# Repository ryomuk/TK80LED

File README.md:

# TK80LED
TK-80互換機(ZK-80P)用LED表示盤(TK-80 flavor LED board for ZK-80P)

## 概要
オレンジピコショップで売られているTK-80互換機(ZK-80 ポケット(ZK-80P))用の表示盤
「TK-80 flavor LED board for ZK-80P」です．

オリジナルのキットの表示がTK-80っぽくなかったので，SN713を使って本物っぽくしてみました．
ZK-80ポケット(ZK-80P)用です．ZK-80には対応していません．

私が勝手に作ったもので，ZK-80, ZK-80Pの作者様やピコソフト様とは無関係です．

## 基板
配線パターン，LED配置，シルクはかなり実機に似せたこだわりの作り(笑)になっています．

## ファームウェア書き換えについて
ZK-80PはMAX7219の輝度の設定値が小さいので，そのままの設定でSN713を駆動するとかなり暗いです．
明るくするためには，ZK-80Pのファームウェアを書き換えが必要です．
ファームウェアの書き換えについては下記のブログをご参照下さい．

ファームウェア書き換え後

実機との比較

ファームウェア書き換え前

## 関連ブログ
 - [ZK-80(TK-80互換機)のLED改装](https://blog.goo.ne.jp/tk-80/e/5548a42761d789a6131d8d7753d236a3)

## 免責事項
- 本機によってZK-80Pに不具合等が発生しても一切関知しません．

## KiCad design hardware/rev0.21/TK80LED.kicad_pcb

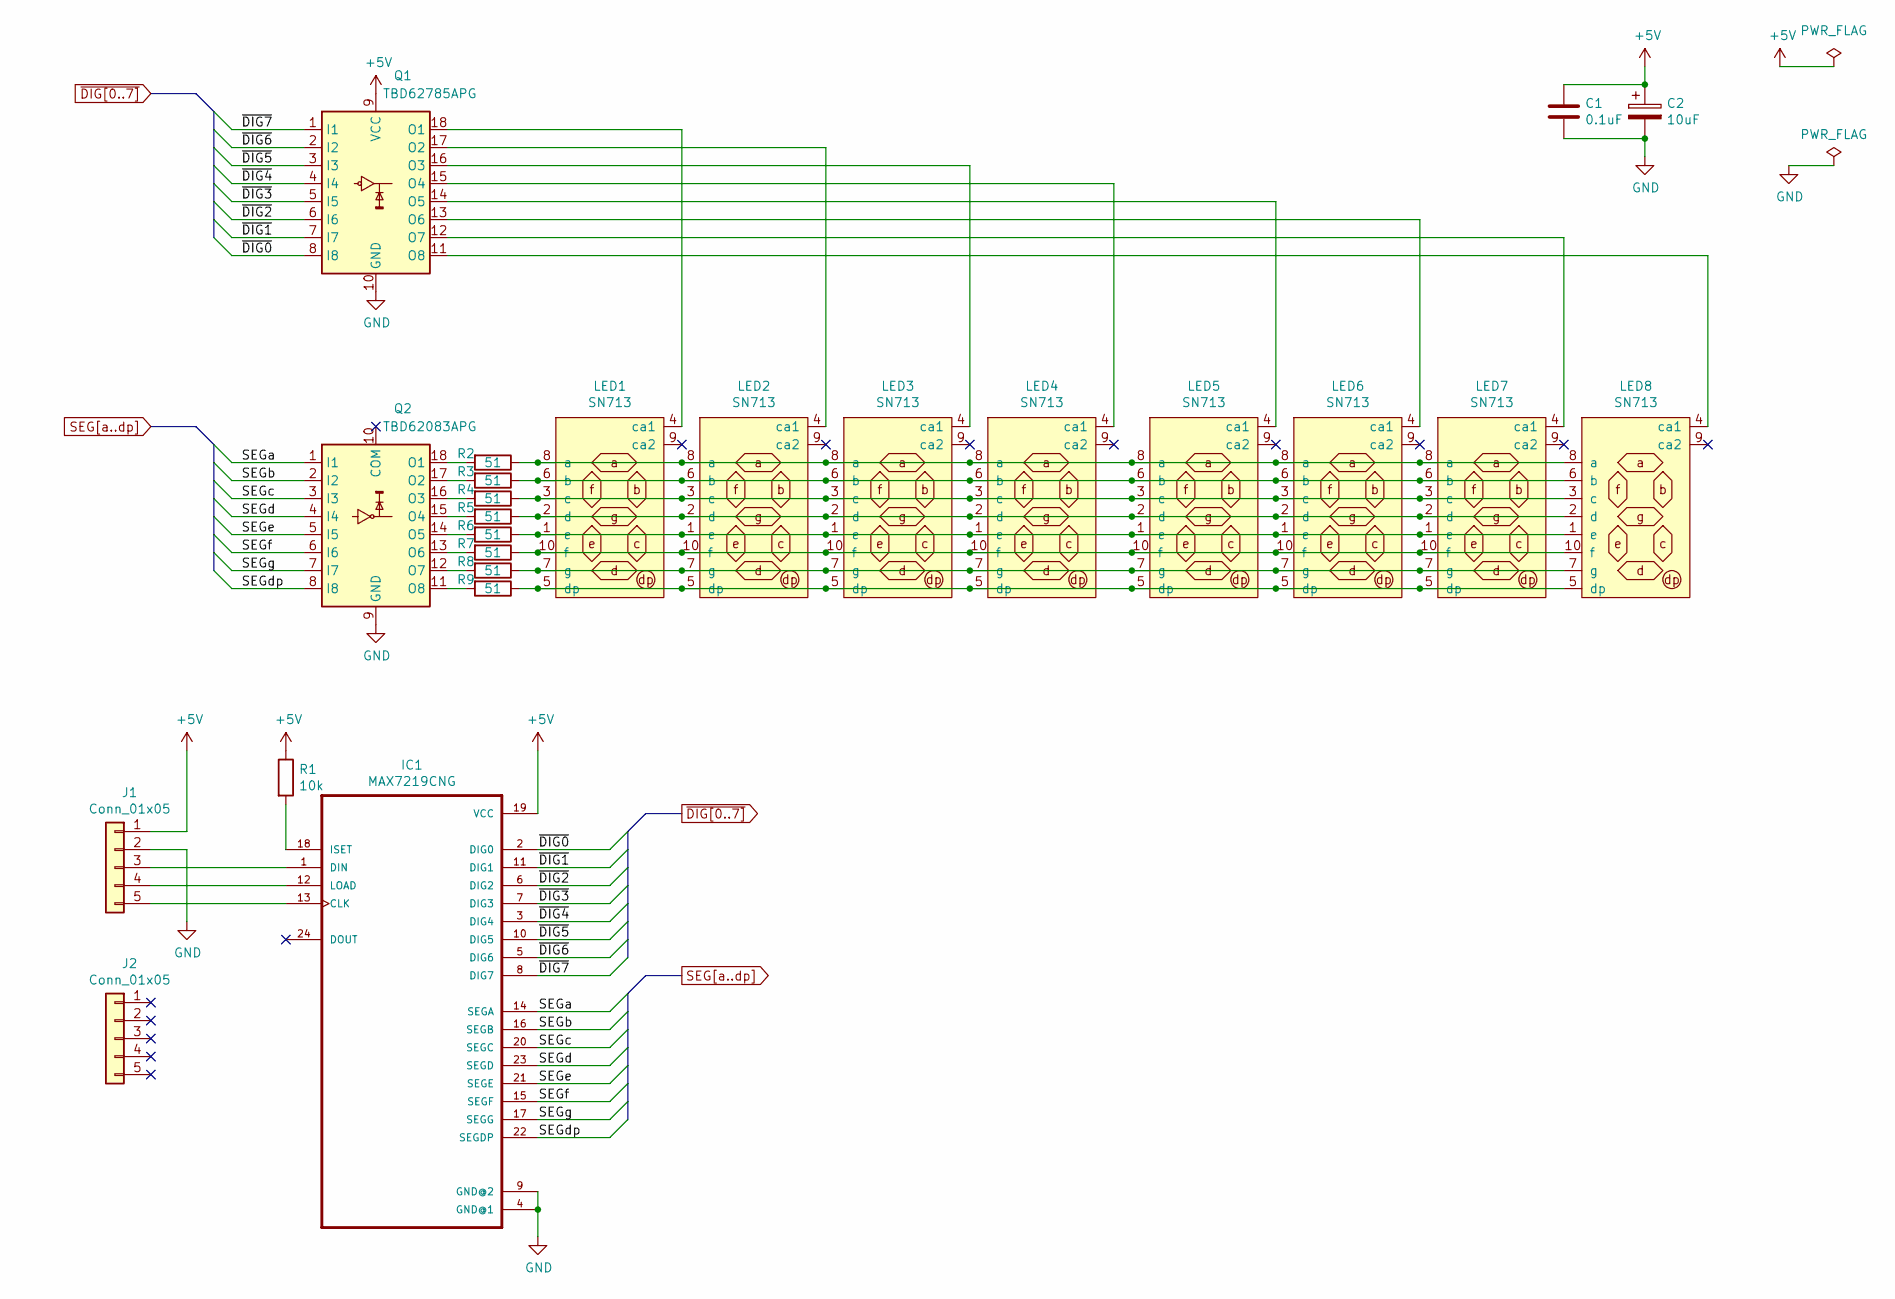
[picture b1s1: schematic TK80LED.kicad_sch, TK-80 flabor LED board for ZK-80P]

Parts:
C1: 0.1uF; C_Disc_D3.0mm_W1.6mm_P2.50mm
C2: 10uF; CP_Radial_D4.0mm_P1.50mm
IC1: MAX7219CNG; DIP794W47P254L3213H457Q24
J1, J2: Conn_01x05; SIP-5
LED1, LED2, LED3, LED4, LED5, LED6, LED7, LED8: SN713; DIP-10_800_ELL_LED
Q1: TBD62785APG; DIP-18_296_ELL
Q2: TBD62083APG; DIP-18_296_ELL
R1: 10k; R_Axial_DIN0207_L6.3mm_D2.5mm_P10.16mm_Horizontal
R2, R3, R4, R5, R6, R7, R8, R9: 51; R_Axial_DIN0207_L6.3mm_D2.5mm_P10.16mm_Horizontal

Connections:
+5V: C1.1, C2.1, IC1.19 (VCC), J1.1, Q1.9 (VCC), R1.1
/SEGa: IC1.14 (SEGA), Q2.1 (I1)
/SEGb: IC1.16 (SEGB), Q2.2 (I2)
/SEGc: IC1.20 (SEGC), Q2.3 (I3)
/SEGd: IC1.23 (SEGD), Q2.4 (I4)
/SEGdp: IC1.22 (SEGDP), Q2.8 (I8)
/SEGe: IC1.21 (SEGE), Q2.5 (I5)
/SEGf: IC1.15 (SEGF), Q2.6 (I6)
/SEGg: IC1.17 (SEGG), Q2.7 (I7)
GND: C1.2, C2.2, IC1.4 (GND@1), IC1.9 (GND@2), J1.2, Q1.10 (GND), Q2.9 (GND)
unnamed: IC1.1 (DIN), J1.3
unnamed: IC1.12 (LOAD), J1.4
unnamed: IC1.13 (CLK), J1.5
unnamed: IC1.18 (ISET), R1.2
unnamed: LED1.1 (e), LED2.1 (e), LED3.1 (e), LED4.1 (e), LED5.1 (e), LED6.1 (e), LED7.1 (e), LED8.1 (e), R6.1
unnamed: LED1.2 (d), LED2.2 (d), LED3.2 (d), LED4.2 (d), LED5.2 (d), LED6.2 (d), LED7.2 (d), LED8.2 (d), R5.1
unnamed: LED1.3 (c), LED2.3 (c), LED3.3 (c), LED4.3 (c), LED5.3 (c), LED6.3 (c), LED7.3 (c), LED8.3 (c), R4.1
unnamed: LED1.4 (ca1), Q1.18 (O1)
unnamed: LED1.5 (dp), LED2.5 (dp), LED3.5 (dp), LED4.5 (dp), LED5.5 (dp), LED6.5 (dp), LED7.5 (dp), LED8.5 (dp), R9.1
unnamed: LED1.6 (b), LED2.6 (b), LED3.6 (b), LED4.6 (b), LED5.6 (b), LED6.6 (b), LED7.6 (b), LED8.6 (b), R3.1
unnamed: LED1.7 (g), LED2.7 (g), LED3.7 (g), LED4.7 (g), LED5.7 (g), LED6.7 (g), LED7.7 (g), LED8.7 (g), R8.1
unnamed: LED1.8 (a), LED2.8 (a), LED3.8 (a), LED4.8 (a), LED5.8 (a), LED6.8 (a), LED7.8 (a), LED8.8 (a), R2.1
unnamed: LED1.10 (f), LED2.10 (f), LED3.10 (f), LED4.10 (f), LED5.10 (f), LED6.10 (f), LED7.10 (f), LED8.10 (f), R7.1
unnamed: LED2.4 (ca1), Q1.17 (O2)
unnamed: LED3.4 (ca1), Q1.16 (O3)
unnamed: LED4.4 (ca1), Q1.15 (O4)
unnamed: LED5.4 (ca1), Q1.14 (O5)
unnamed: LED6.4 (ca1), Q1.13 (O6)
unnamed: LED7.4 (ca1), Q1.12 (O7)
unnamed: LED8.4 (ca1), Q1.11 (O8)
unnamed: Q2.11 (O8), R9.2
unnamed: Q2.12 (O7), R8.2
unnamed: Q2.13 (O6), R7.2
unnamed: Q2.14 (O5), R6.2
unnamed: Q2.15 (O4), R5.2
unnamed: Q2.16 (O3), R4.2
unnamed: Q2.17 (O2), R3.2
unnamed: Q2.18 (O1), R2.2
~DIG0: IC1.2 (DIG0), Q1.8 (I8)
~DIG1: IC1.11 (DIG1), Q1.7 (I7)
~DIG2: IC1.6 (DIG2), Q1.6 (I6)
~DIG3: IC1.7 (DIG3), Q1.5 (I5)
~DIG4: IC1.3 (DIG4), Q1.4 (I4)
~DIG5: IC1.10 (DIG5), Q1.3 (I3)
~DIG6: IC1.5 (DIG6), Q1.2 (I2)
~DIG7: IC1.8 (DIG7), Q1.1 (I1)

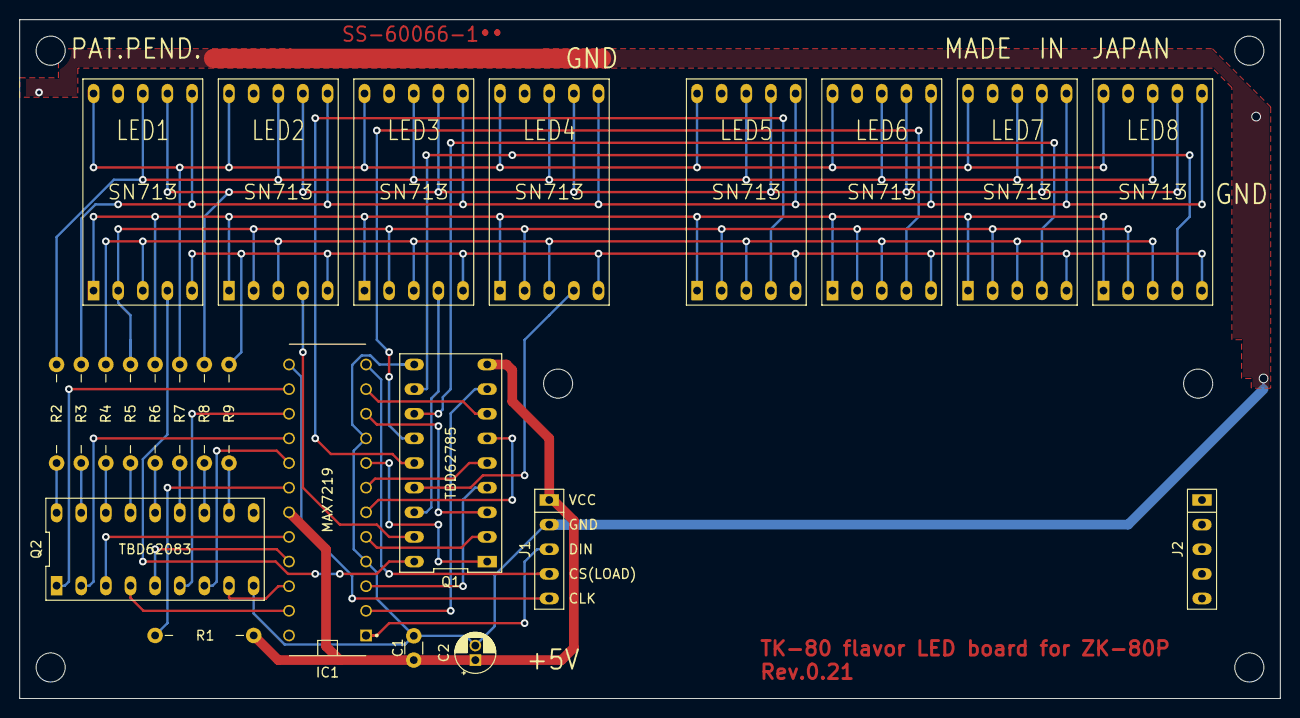
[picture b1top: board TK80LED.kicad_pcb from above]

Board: 2 copper layers, 130.0 x 70.0 mm, 30 parts (0 on the bottom side), 46 nets.

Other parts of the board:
REF1, REF2, REF3, REF4, REF5, REF6: MountingHole_3mm

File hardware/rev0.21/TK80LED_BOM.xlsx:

部品表ブヒンヒョウ
Item | Qty | Reference(s) | Value | 備考ビコウ
1 | 1 | C1 | 0.1uF
2 | 1 | C2 | 10uF
3 | 1 | IC1 | MAX7219CNG
4 | 2 | J1, J2 | Conn_01x05 | ピンヘッダ、ピンソケット等、接続方法にあわせて任意トウセツゾクホウホウニンイ
5 | 8 | LED1, LED2, LED3, LED4, LED5, LED6, LED7, LED8 | SN713B | SN713A(入手困難)でも可ニュウシュコンナンカ
6 | 1 | Q1 | TBD62785APG
7 | 1 | Q2 | TBD62083APG
8 | 1 | R1 | 10kΩ, 1/4W
9 | 8 | R2, R3, R4, R5, R6, R7, R8, R9 | 51Ω, 1/4W

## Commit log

2023-05-29 gerber updated
2024-03-26 readme updated
